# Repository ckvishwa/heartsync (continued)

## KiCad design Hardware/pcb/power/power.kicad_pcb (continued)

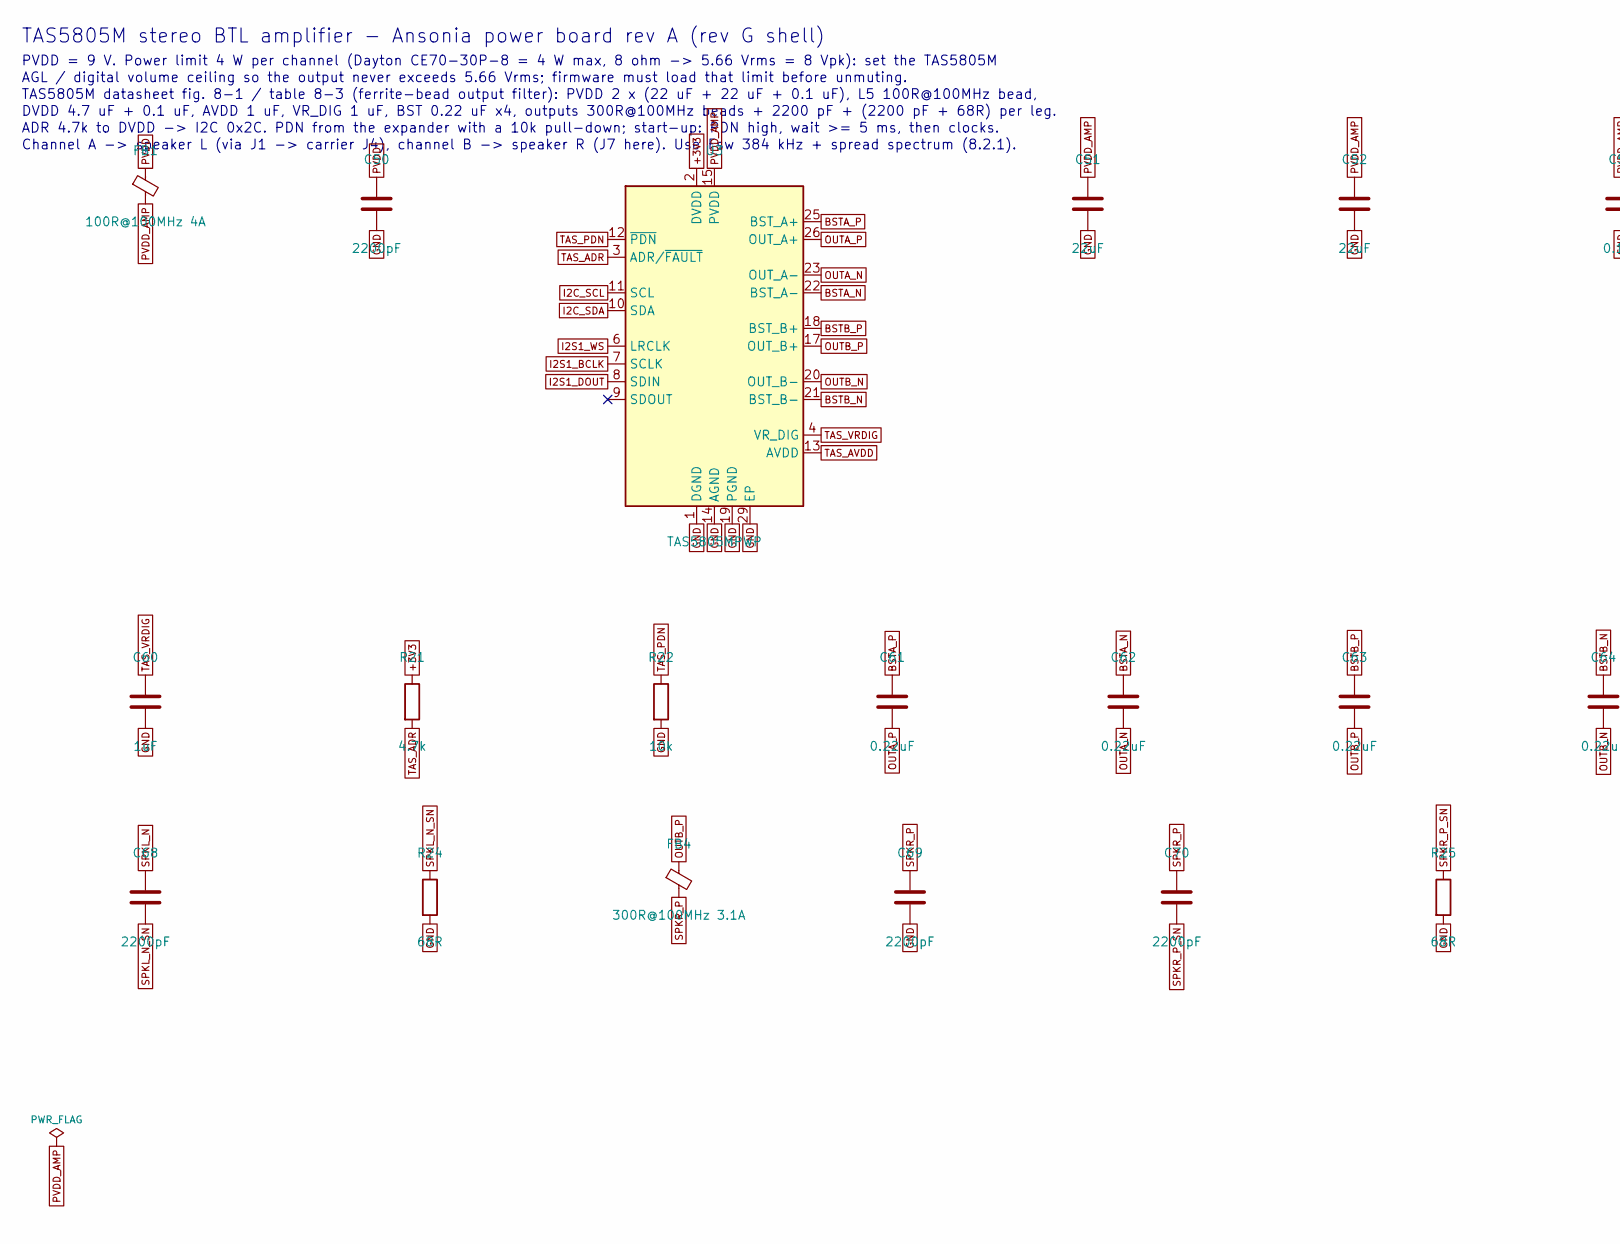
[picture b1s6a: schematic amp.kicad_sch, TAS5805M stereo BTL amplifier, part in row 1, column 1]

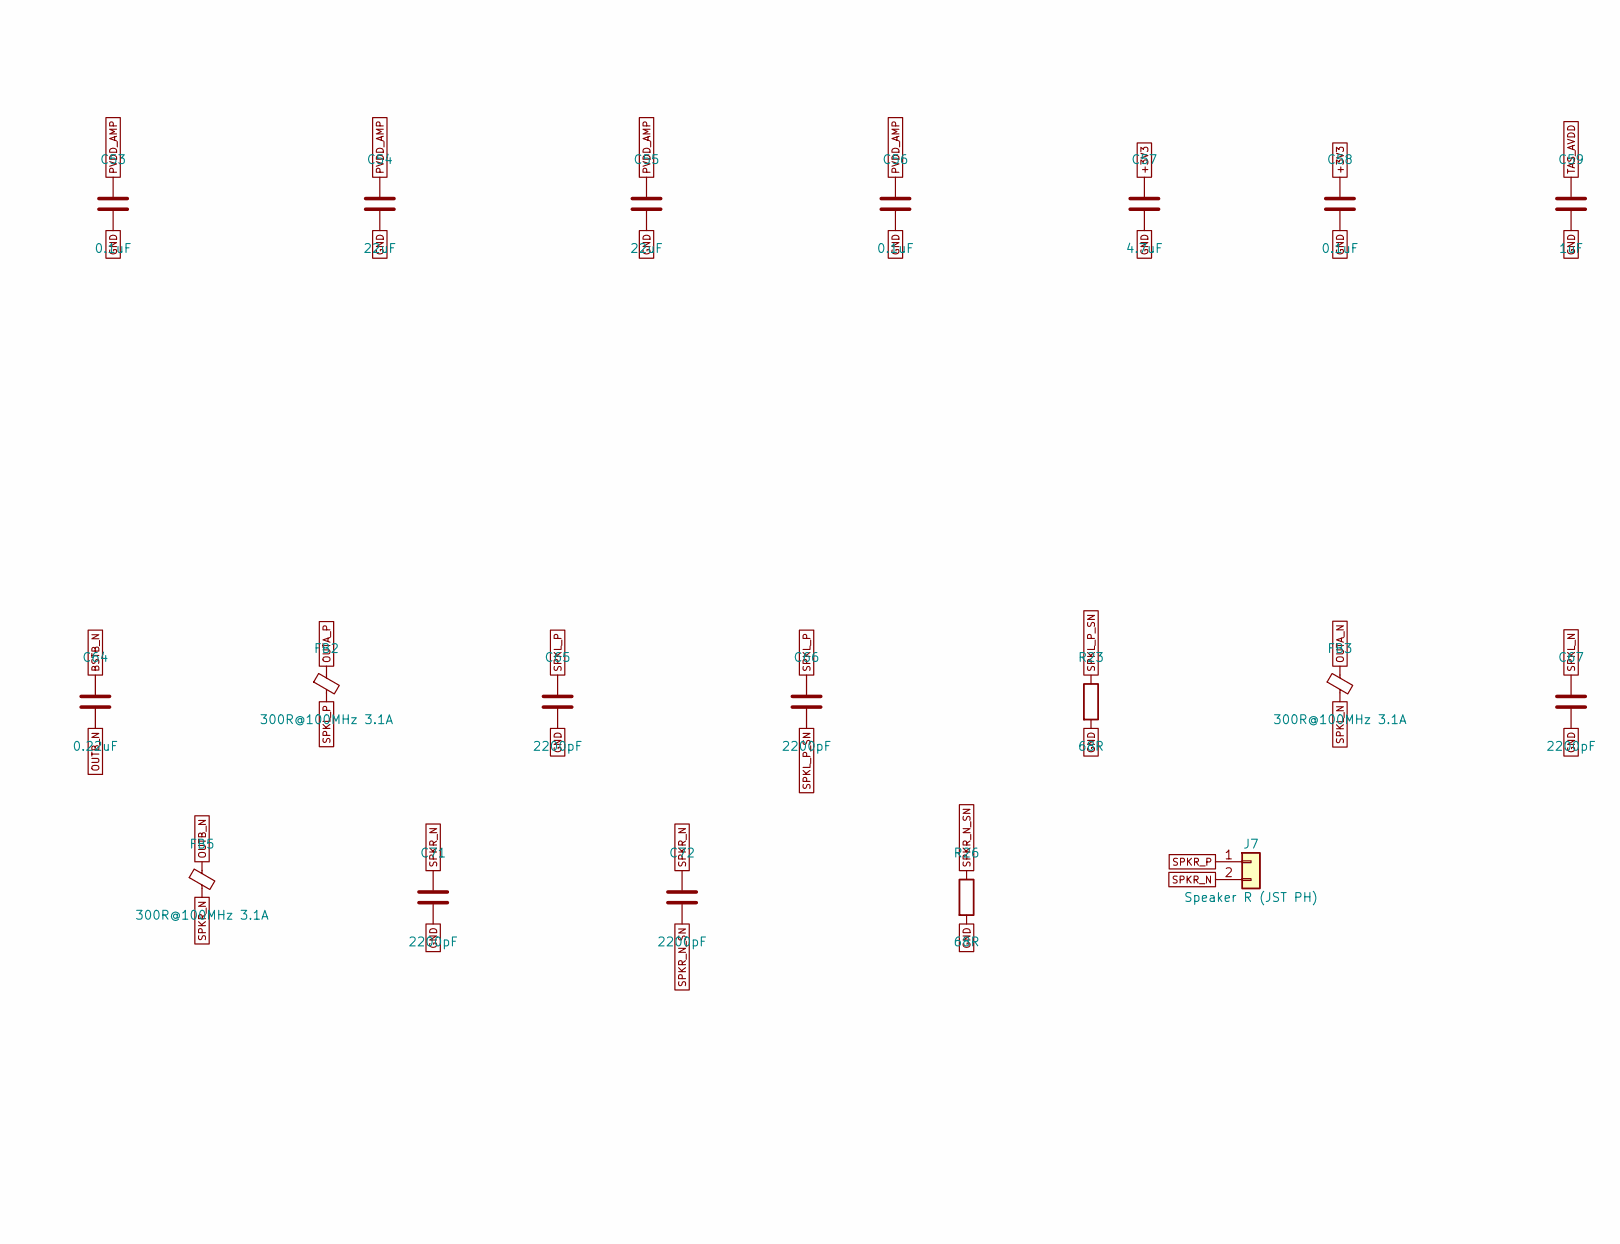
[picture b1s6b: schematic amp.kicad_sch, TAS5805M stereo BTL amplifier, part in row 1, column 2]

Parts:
C50: 2200pF; C_0402_1005Metric
C51, C52, C54, C55: 22uF; C_0805_2012Metric
C53, C56, C58: 0.1uF; C_0402_1005Metric
C57: 4.7uF; C_0603_1608Metric
C59, C60: 1uF; C_0603_1608Metric
C61, C62, C63, C64: 0.22uF; C_0603_1608Metric
C65, C66, C67, C68, C69, C70, C71, C72: 2200pF; C_0603_1608Metric
FB1: 100R@100MHz 4A; L_0805_2012Metric
FB2, FB3, FB4, FB5: 300R@100MHz 3.1A; L_0805_2012Metric
J7: Speaker R (JST PH); JST_PH_S2B-PH-SM4-TB_1x02-1MP_P2.00mm_Horizontal
R21: 4.7k; R_0402_1005Metric
R22: 10k; R_0402_1005Metric
R23, R24, R25, R26: 68R; R_0603_1608Metric
U3: TAS5805MPWP; TI_PWP0028M_HTSSOP-28_ThermalVias_0.3; MPN TAS5805MPWPR; LCSC C2059816

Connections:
+3V3: C57.1, C58.1, R21.1, U3.2 (DVDD); also elsewhere on the board
BSTA_N: C62.1, U3.22 (BST_A-)
BSTA_P: C61.1, U3.25 (BST_A+)
BSTB_N: C64.1, U3.21 (BST_B-)
BSTB_P: C63.1, U3.18 (BST_B+)
GND: C50.2, C51.2, C52.2, C53.2, C54.2, C55.2, C56.2, C57.2, C58.2, C59.2, C60.2, C65.2, C67.2, C69.2, C71.2, R22.2, R23.2, R24.2, R25.2, R26.2, U3.1 (DGND), U3.5 (DGND), U3.14 (AGND), U3.19 (PGND), U3.24 (PGND), U3.29 (EP); also elsewhere on the board
I2C_SCL: U3.11 (SCL); also elsewhere on the board
I2C_SDA: U3.10 (SDA); also elsewhere on the board
I2S1_BCLK: U3.7 (SCLK); also elsewhere on the board
I2S1_DOUT: U3.8 (SDIN); also elsewhere on the board
I2S1_WS: U3.6 (LRCLK); also elsewhere on the board
OUTA_N: C62.2, FB3.1, U3.23 (OUT_A-)
OUTA_P: C61.2, FB2.1, U3.26 (OUT_A+)
OUTB_N: C64.2, FB5.1, U3.20 (OUT_B-)
OUTB_P: C63.2, FB4.1, U3.17 (OUT_B+)
PVDD: C50.1, FB1.1; also elsewhere on the board
PVDD_AMP: C51.1, C52.1, C53.1, C54.1, C55.1, C56.1, FB1.2, U3.15 (PVDD), U3.16 (PVDD), U3.27 (PVDD), U3.28 (PVDD)
SPKL_N: C67.1, C68.1, FB3.2; also elsewhere on the board
SPKL_N_SN: C68.2, R24.1
SPKL_P: C65.1, C66.1, FB2.2; also elsewhere on the board
SPKL_P_SN: C66.2, R23.1
SPKR_N: C71.1, C72.1, FB5.2, J7.2
SPKR_N_SN: C72.2, R26.1
SPKR_P: C69.1, C70.1, FB4.2, J7.1
SPKR_P_SN: C70.2, R25.1
TAS_ADR: R21.2, U3.3 (ADR/~FAULT)
TAS_AVDD: C59.1, U3.13 (AVDD)
TAS_PDN: R22.1, U3.12 (~PDN); also elsewhere on the board
TAS_VRDIG: C60.1, U3.4 (VR_DIG)

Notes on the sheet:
TAS5805M stereo BTL amplifier - Ansonia power board rev A (rev G shell)
PVDD = 9 V. Power limit 4 W per channel (Dayton CE70-30P-8 = 4 W max, 8 ohm -> 5.66 Vrms = 8 Vpk): set the TAS5805M
AGL / digital volume ceiling so the output never exceeds 5.66 Vrms; firmware must load that limit before unmuting.
TAS5805M datasheet fig. 8-1 / table 8-3 (ferrite-bead output filter): PVDD 2 x (22 uF + 22 uF + 0.1 uF), L5 100R@100MHz bead,
DVDD 4.7 uF + 0.1 uF, AVDD 1 uF, VR_DIG 1 uF, BST 0.22 uF x4, outputs 300R@100MHz beads + 2200 pF + (2200 pF + 68R) per leg.
ADR 4.7k to DVDD -> I2C 0x2C. PDN from the expander with a 10k pull-down; start-up: PDN high, wait >= 5 ms, then clocks.
Channel A -> speaker L (via J1 -> carrier J4), channel B -> speaker R (J7 here). Use Fsw 384 kHz + spread spectrum (8.2.1).

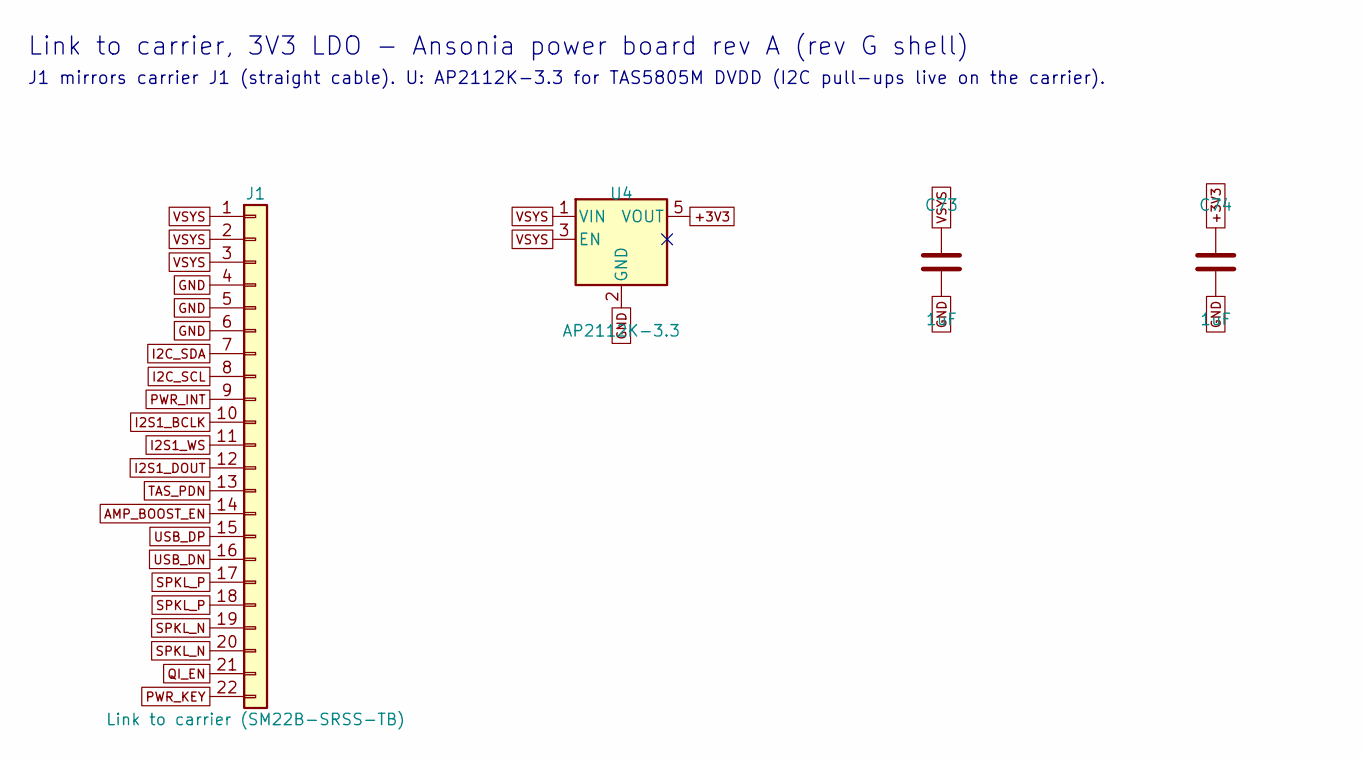
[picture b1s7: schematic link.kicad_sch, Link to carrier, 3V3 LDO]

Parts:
C73, C74: 1uF; C_0402_1005Metric
J1: Link to carrier (SM22B-SRSS-TB); JST_SH_SM22B-SRSS-TB_1x22-1MP_P1.00mm_Horizontal
U4: AP2112K-3.3; SOT-23-5; MPN AP2112K-3.3TRG1; LCSC C51118

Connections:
+3V3: C74.1, U4.5 (VOUT); also elsewhere on the board
AMP_BOOST_EN: J1.14; also elsewhere on the board
GND: C73.2, C74.2, J1.4, J1.5, J1.6, U4.2 (GND); also elsewhere on the board
I2C_SCL: J1.8; also elsewhere on the board
I2C_SDA: J1.7; also elsewhere on the board
I2S1_BCLK: J1.10; also elsewhere on the board
I2S1_DOUT: J1.12; also elsewhere on the board
I2S1_WS: J1.11; also elsewhere on the board
PWR_INT: J1.9; also elsewhere on the board
PWR_KEY: J1.22; also elsewhere on the board
QI_EN: J1.21; also elsewhere on the board
SPKL_N: J1.19, J1.20; also elsewhere on the board
SPKL_P: J1.17, J1.18; also elsewhere on the board
TAS_PDN: J1.13; also elsewhere on the board
USB_DN: J1.16; also elsewhere on the board
USB_DP: J1.15; also elsewhere on the board
VSYS: C73.1, J1.1, J1.2, J1.3, U4.1 (VIN), U4.3 (EN); also elsewhere on the board

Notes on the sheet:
Link to carrier, 3V3 LDO - Ansonia power board rev A (rev G shell)
J1 mirrors carrier J1 (straight cable). U: AP2112K-3.3 for TAS5805M DVDD (I2C pull-ups live on the carrier).

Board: 4 copper layers, 130 parts (38 on the bottom side), 74 nets, no tracks yet.

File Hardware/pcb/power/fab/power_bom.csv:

Comment,Designator,Footprint,LCSC Part #,MPN,Qty
10uF,"C1,C2,C48,C49",C_0805_2012Metric,,,4
10uF,"C24,C37",C_0603_1608Metric,,,2
4.7uF,"C27,C40,C57",C_0603_1608Metric,,,3
47nF,"C28,C41",C_0402_1005Metric,,,2
8.2nF,"C29,C42",C_0402_1005Metric,,,2
2.2uF,"C15,C16,C18,C19,C3",C_0603_1608Metric,,,5
22uF,"C31,C32,C33,C44,C45,C46",C_1206_3216Metric,,,6
1uF,"C34,C47,C59,C60",C_0603_1608Metric,,,4
0.1uF,"C11,C13,C14,C17,C20,C25,C26,C38,C39,C4,C53,C56,C58",C_0402_1005Metric,,,13
22uF,"C10,C12,C21,C22,C23,C35,C36,C5,C51,C52,C54,C55,C6,C7,C8,C9",C_0805_2012Metric,,,16
2200pF,C50,C_0402_1005Metric,,,1
0.22uF,"C61,C62,C63,C64",C_0603_1608Metric,,,4
2200pF,"C65,C66,C67,C68,C69,C70,C71,C72",C_0603_1608Metric,,,8
1uF,"C73,C74",C_0402_1005Metric,,,2
SMF22A,"D1,D2",D_SOD-123F,,,2
SMF5.0A,D3,D_SOD-123F,,,1
8A fast,F1,Fuse_1206_3216Metric,,0466008.NR,1
100R@100MHz 4A,FB1,L_0805_2012Metric,,,1
300R@100MHz 3.1A,"FB2,FB3,FB4,FB5",L_0805_2012Metric,,,4
Link to carrier (SM22B-SRSS-TB),J1,JST_SH_SM22B-SRSS-TB_1x22-1MP_P1.00mm_Horizontal,,,1
"124019572112A (port 1, in/out)",J2,USB_C_Amphenol_124019572112A,,124019572112A,1
"124019572112A (port 2, out)",J3,USB_C_Amphenol_124019572112A,,124019572112A,1
"Cell: Amass MR30PW-M (3-pole; pins 1 = BAT+, 3 = BAT-, 2 open)",J4,Amass_MR30PW-M_1x03_P3.50mm_Horizontal,,MR30PW-M,1
Cell NTC (JST SH 2),J5,JST_SH_SM02B-SRSS-TB_1x02-1MP_P1.00mm_Horizontal,,,1
"Qi TX module 24x32 (9 V, 2 contacts per leg)",J6,JST_SH_SM04B-SRSS-TB_1x04-1MP_P1.00mm_Horizontal,,,1
Speaker R (JST PH),J7,JST_PH_S2B-PH-SM4-TB_1x02-1MP_P2.00mm_Horizontal,,,1
2.2uH,"L1,L2,L3",L_Bourns_SRP7028A_7.3x6.6mm,,SRP7028A-2R2M,3
1uH,L4,L_1210_3225Metric,,DFE322520F-1R0M,1
DMP3013SFV,Q1,Diodes_PowerDI3333-8,,,1
3.3k,"R1,R2",R_0402_1005Metric,,,2
232k,"R10,R16",R_0402_1005Metric,,,2
49.9k,"R11,R17",R_0402_1005Metric,,,2
23.7k,"R12,R18",R_0402_1005Metric,,,2
499k,"R13,R19",R_0402_1005Metric,,,2
76.8k,"R14,R20",R_0402_1005Metric,,,2
4.7k,R21,R_0402_1005Metric,,,1
68R,"R23,R24,R25,R26",R_0603_1608Metric,,,4
510k,R3,R_0402_1005Metric,,,1
22.1k,R4,R_0402_1005Metric,,,1
22k,"R5,R6",R_0402_1005Metric,,,2
10k,"R15,R22,R7,R9",R_0402_1005Metric,,,4
0R,R8,R_1206_3216Metric,,,1
IP5356M_LBZ_CB,U1,QFN-40-1EP_6x6mm_P0.5mm_EP4.6x4.6mm,C46550232,IP5356M_LBZ_CB,1
TPS61088RHLR,"U2,U7",Texas_VQFN-RHL-20,C88281,TPS61088RHLR,2
TAS5805MPWP,U3,TI_PWP0028M_HTSSOP-28_ThermalVias_0.3,C2059816,TAS5805MPWPR,1
AP2112K-3.3,U4,SOT-23-5,C51118,AP2112K-3.3TRG1,1
TPD4E05U06DQA,"U5,U6",USON-10_2.5x1.0mm_P0.5mm,,TPD4E05U06DQAR,2

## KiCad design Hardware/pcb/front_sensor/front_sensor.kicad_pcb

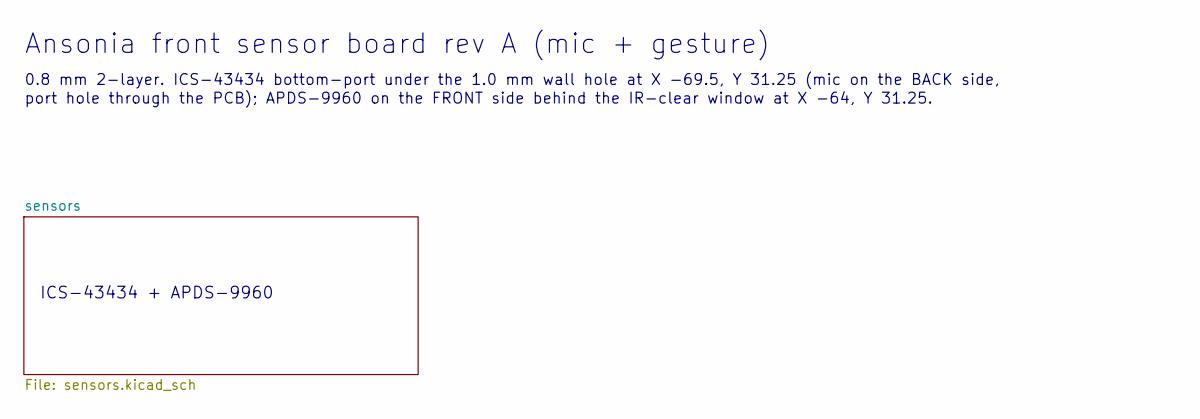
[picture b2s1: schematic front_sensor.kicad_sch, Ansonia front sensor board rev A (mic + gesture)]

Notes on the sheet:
ICS-43434 + APDS-9960
Ansonia front sensor board rev A (mic + gesture)
0.8 mm 2-layer. ICS-43434 bottom-port under the 1.0 mm wall hole at X -69.5, Y 31.25 (mic on the BACK side,
port hole through the PCB); APDS-9960 on the FRONT side behind the IR-clear window at X -64, Y 31.25.

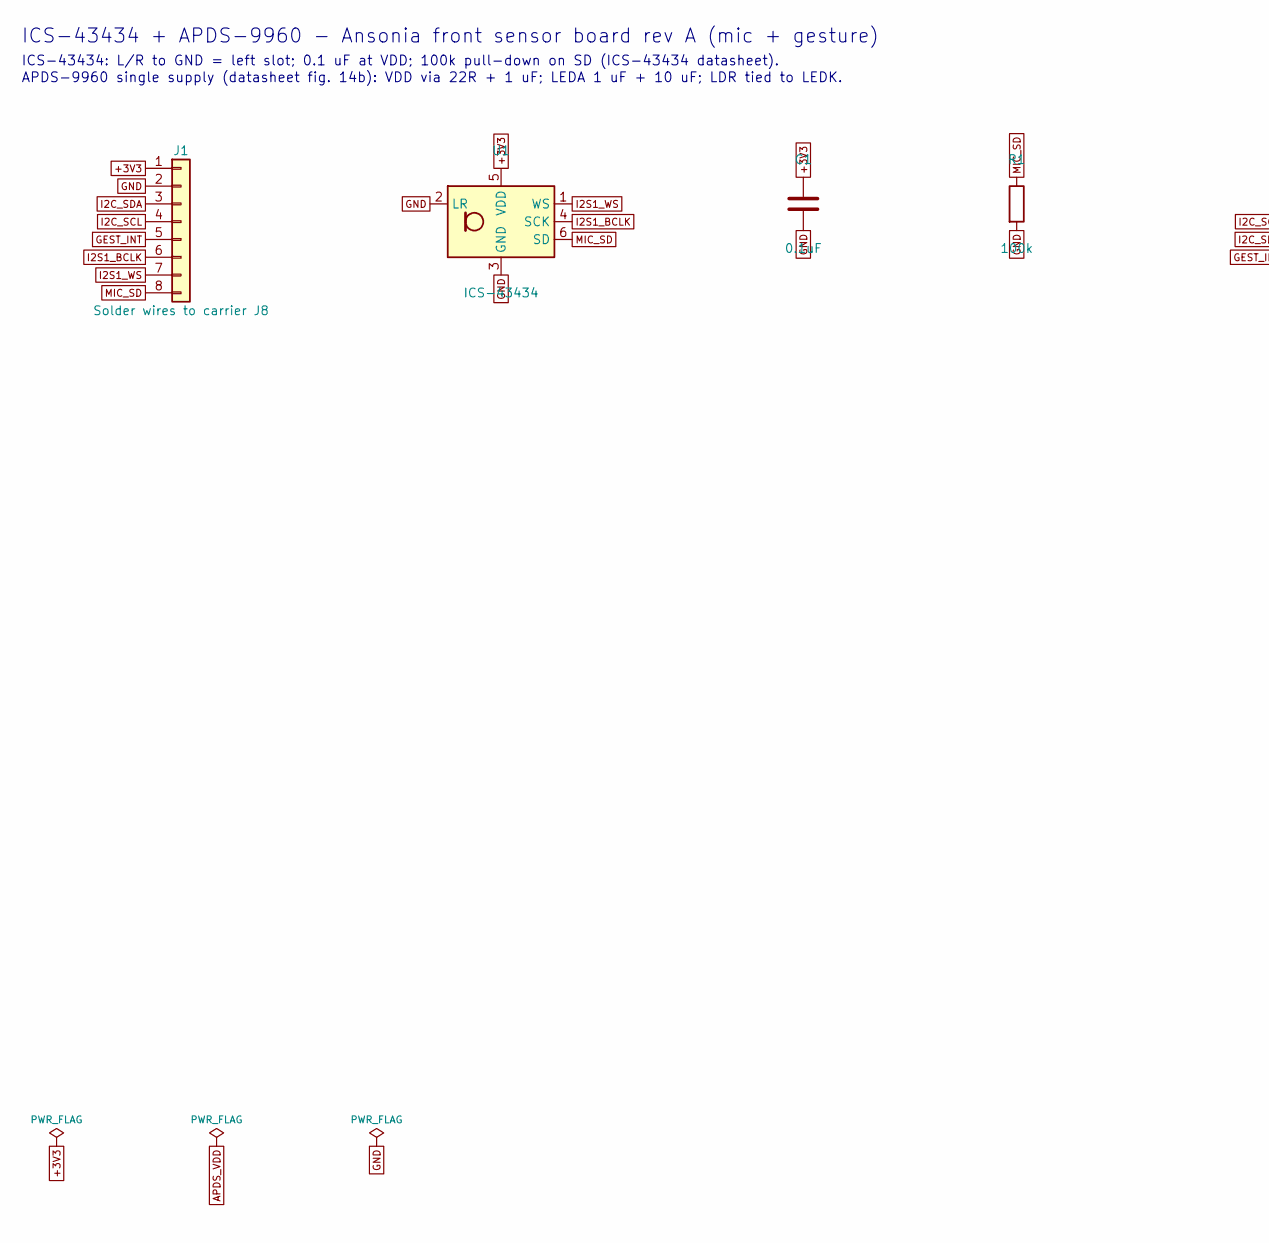
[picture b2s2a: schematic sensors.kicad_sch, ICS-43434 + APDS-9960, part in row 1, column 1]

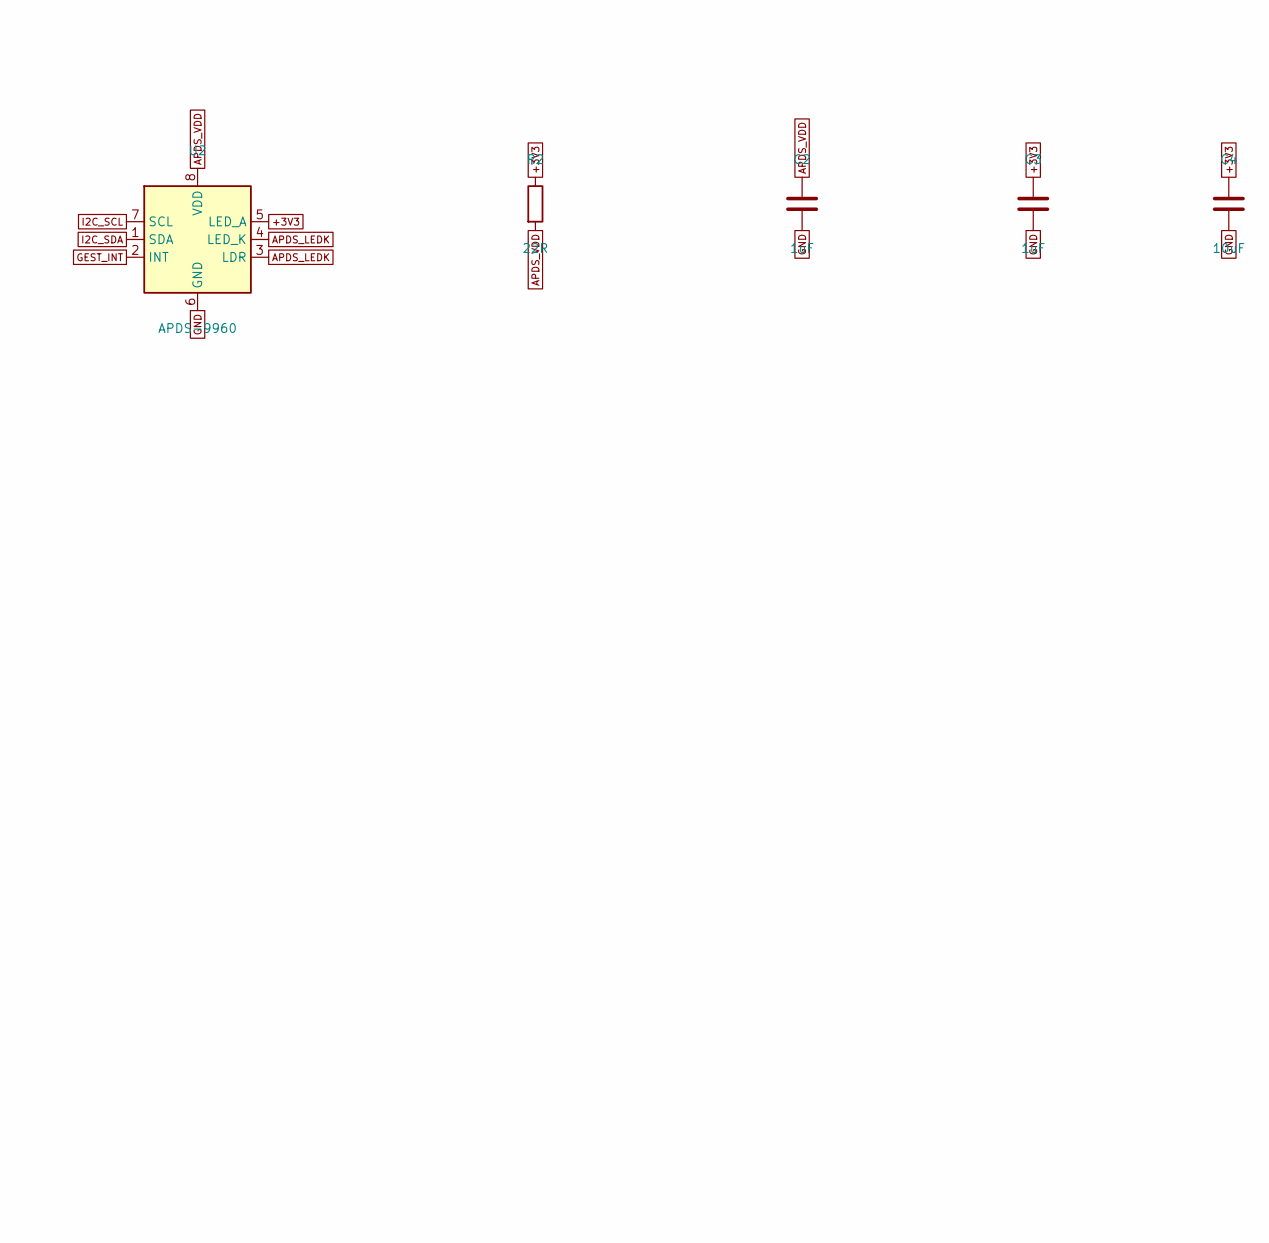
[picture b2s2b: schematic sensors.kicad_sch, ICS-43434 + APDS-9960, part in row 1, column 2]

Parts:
C1: 0.1uF; C_0402_1005Metric
C2, C3: 1uF; C_0402_1005Metric
C4: 10uF; C_0603_1608Metric
J1: Solder wires to carrier J8; WirePads_1x08_P1.20mm
R1: 100k; R_0402_1005Metric
R2: 22R; R_0402_1005Metric
U1: ICS-43434; InvenSense_ICS-43434-6_3.5x2.65mm; MPN ICS-43434
U2: APDS-9960; Avago_APDS-9960; MPN APDS-9960

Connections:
+3V3: C1.1, C3.1, C4.1, J1.1, R2.1, U1.5 (VDD), U2.5 (LED_A)
APDS_LEDK: U2.3 (LDR), U2.4 (LED_K)
APDS_VDD: C2.1, R2.2, U2.8 (VDD)
GEST_INT: J1.5, U2.2 (INT)
GND: C1.2, C2.2, C3.2, C4.2, J1.2, R1.2, U1.2 (LR), U1.3 (GND), U2.6 (GND)
I2C_SCL: J1.4, U2.7 (SCL)
I2C_SDA: J1.3, U2.1 (SDA)
I2S1_BCLK: J1.6, U1.4 (SCK)
I2S1_WS: J1.7, U1.1 (WS)
MIC_SD: J1.8, R1.1, U1.6 (SD)

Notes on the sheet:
ICS-43434 + APDS-9960 - Ansonia front sensor board rev A (mic + gesture)
ICS-43434: L/R to GND = left slot; 0.1 uF at VDD; 100k pull-down on SD (ICS-43434 datasheet).
APDS-9960 single supply (datasheet fig. 14b): VDD via 22R + 1 uF; LEDA 1 uF + 10 uF; LDR tied to LEDK.

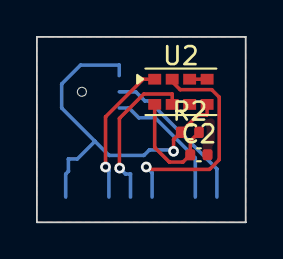
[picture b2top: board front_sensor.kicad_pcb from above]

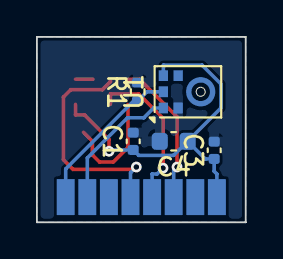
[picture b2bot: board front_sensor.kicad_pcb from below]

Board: 2 copper layers, 11.6 x 10.3 mm, 9 parts (6 on the bottom side), 10 nets.

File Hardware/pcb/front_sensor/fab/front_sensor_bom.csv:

Comment,Designator,Footprint,LCSC Part #,MPN,Qty
0.1uF,C1,C_0402_1005Metric,,,1
1uF,"C2,C3",C_0402_1005Metric,,,2
10uF,C4,C_0603_1608Metric,,,1
Solder wires to carrier J8,J1,WirePads_1x08_P1.20mm,,,1
100k,R1,R_0402_1005Metric,,,1
22R,R2,R_0402_1005Metric,,,1
ICS-43434,U1,InvenSense_ICS-43434-6_3.5x2.65mm,,ICS-43434,1
APDS-9960,U2,Avago_APDS-9960,,APDS-9960,1

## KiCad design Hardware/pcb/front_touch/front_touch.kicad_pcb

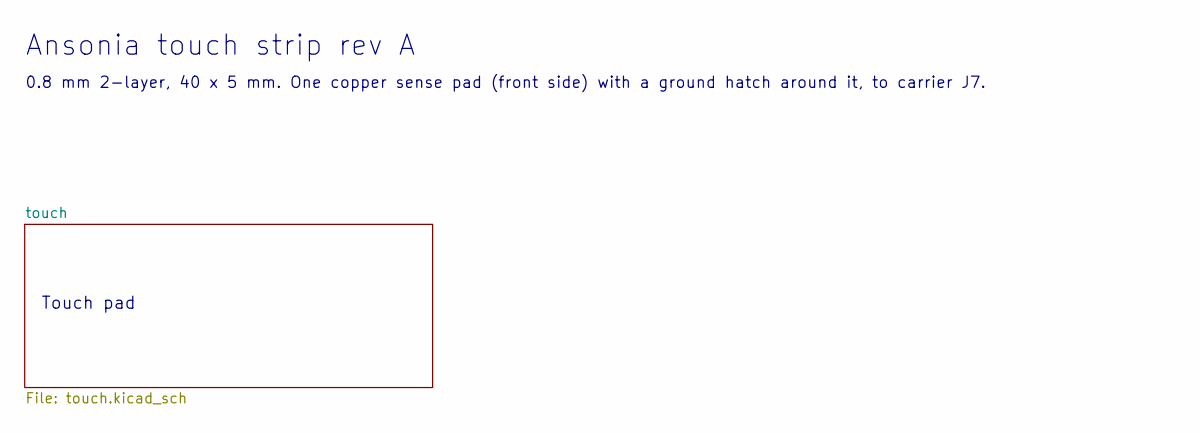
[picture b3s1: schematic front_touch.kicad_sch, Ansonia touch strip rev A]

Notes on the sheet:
Touch pad
Ansonia touch strip rev A
0.8 mm 2-layer, 40 x 5 mm. One copper sense pad (front side) with a ground hatch around it, to carrier J7.

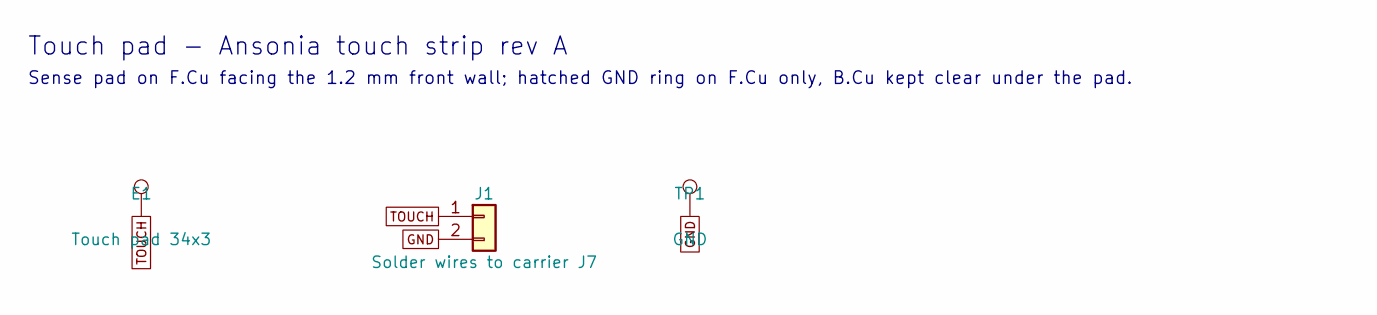
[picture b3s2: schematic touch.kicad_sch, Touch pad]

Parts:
E1: Touch pad 34x3; TouchPad_34x3
J1: Solder wires to carrier J7; WirePads_1x02_P1.60mm
TP1: GND; TestPoint_Pad_D1.0mm

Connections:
GND: J1.2, TP1.1
TOUCH: E1.1, J1.1

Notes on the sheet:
Touch pad - Ansonia touch strip rev A
Sense pad on F.Cu facing the 1.2 mm front wall; hatched GND ring on F.Cu only, B.Cu kept clear under the pad.

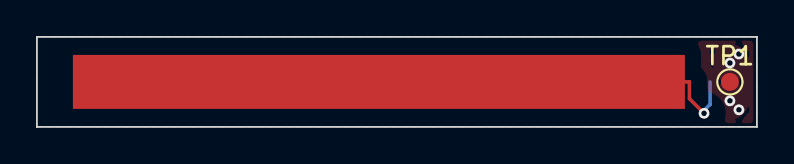
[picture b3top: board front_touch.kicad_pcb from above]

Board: 2 copper layers, 40.0 x 5.0 mm, 3 parts (1 on the bottom side), 2 nets.

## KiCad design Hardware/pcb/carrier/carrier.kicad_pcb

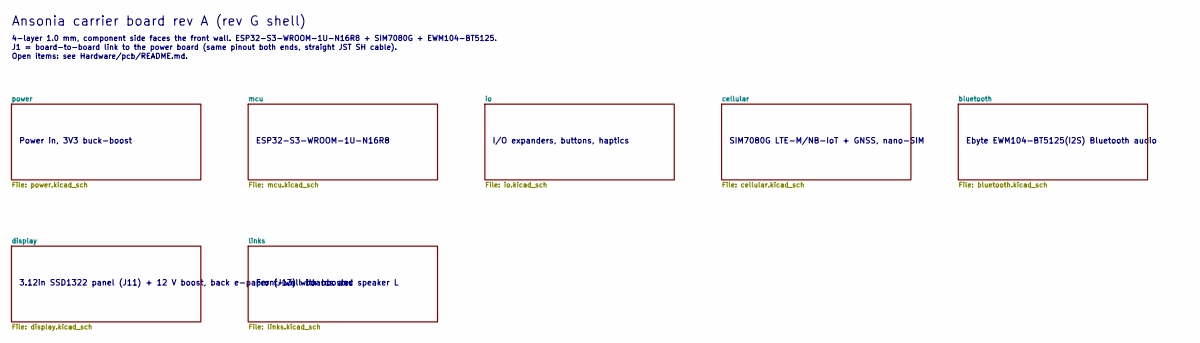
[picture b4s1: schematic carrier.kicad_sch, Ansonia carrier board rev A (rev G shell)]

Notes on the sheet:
Power in, 3V3 buck-boost
ESP32-S3-WROOM-1U-N16R8
I/O expanders, buttons, haptics
SIM7080G LTE-M/NB-IoT + GNSS, nano-SIM
Ebyte EWM104-BT5125(I2S) Bluetooth audio
3.12in SSD1322 panel (J11) + 12 V boost, back e-paper (J13) with booster
Front-wall boards and speaker L
Ansonia carrier board rev A (rev G shell)
4-layer 1.0 mm, component side faces the front wall. ESP32-S3-WROOM-1U-N16R8 + SIM7080G + EWM104-BT5125.
J1 = board-to-board link to the power board (same pinout both ends, straight JST SH cable).
Open items: see Hardware/pcb/README.md.

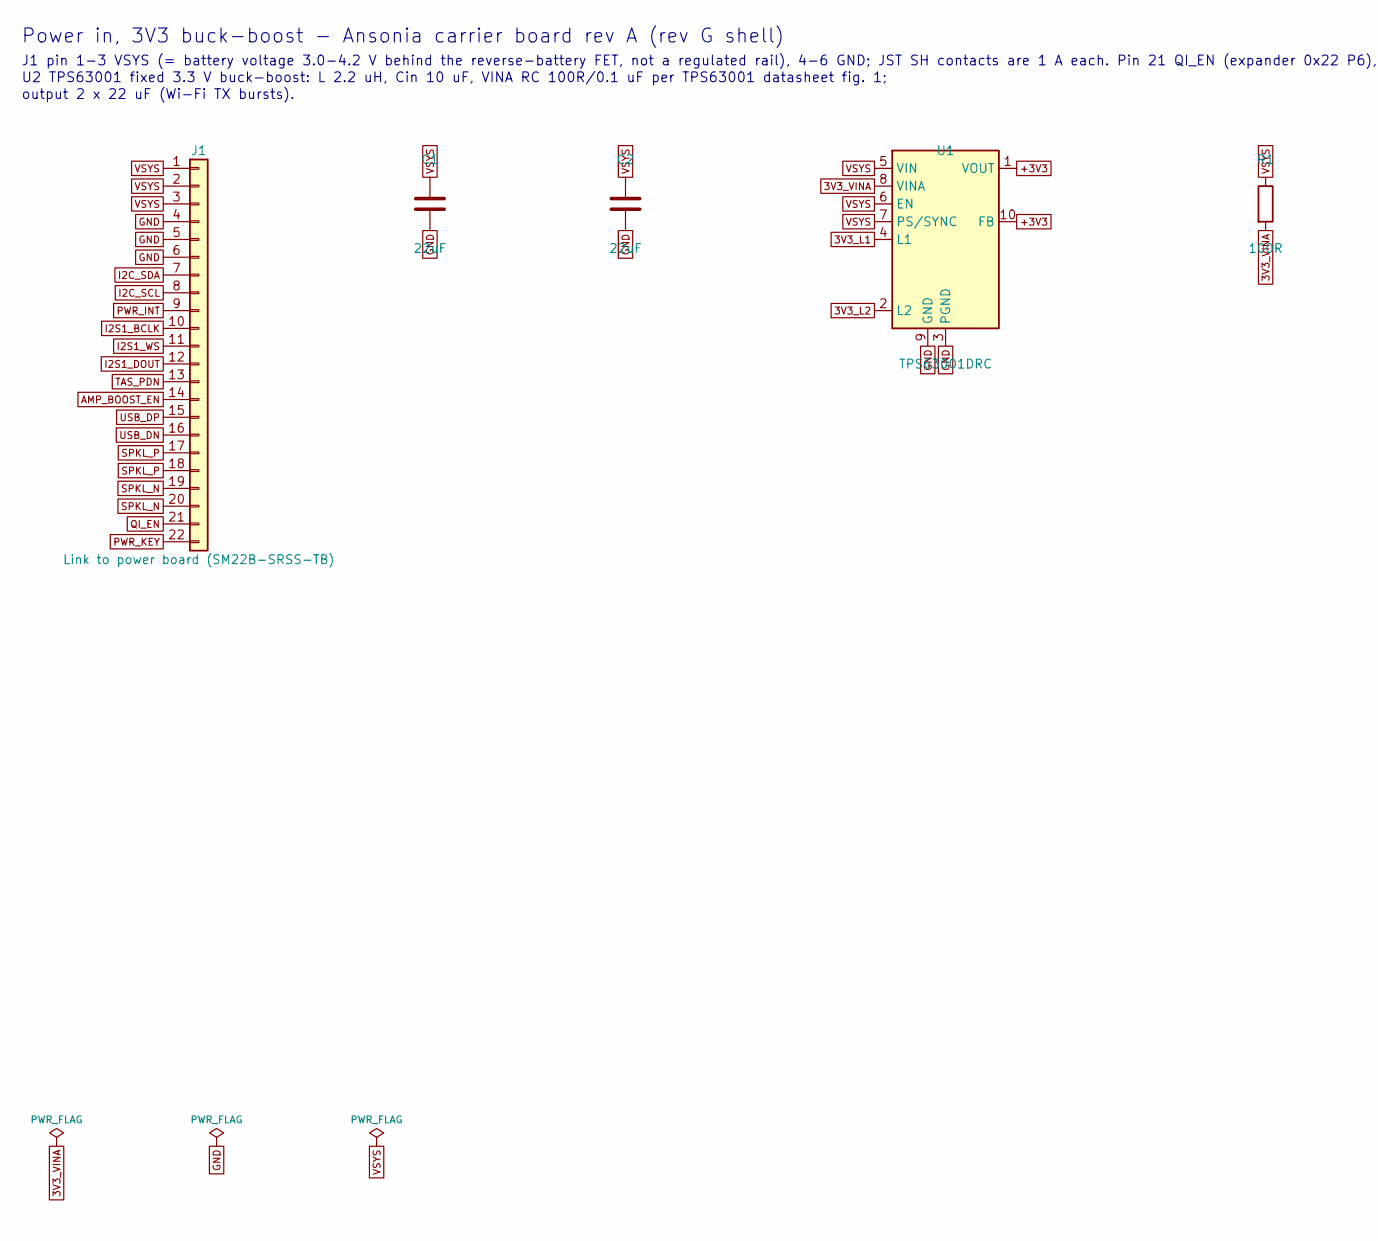
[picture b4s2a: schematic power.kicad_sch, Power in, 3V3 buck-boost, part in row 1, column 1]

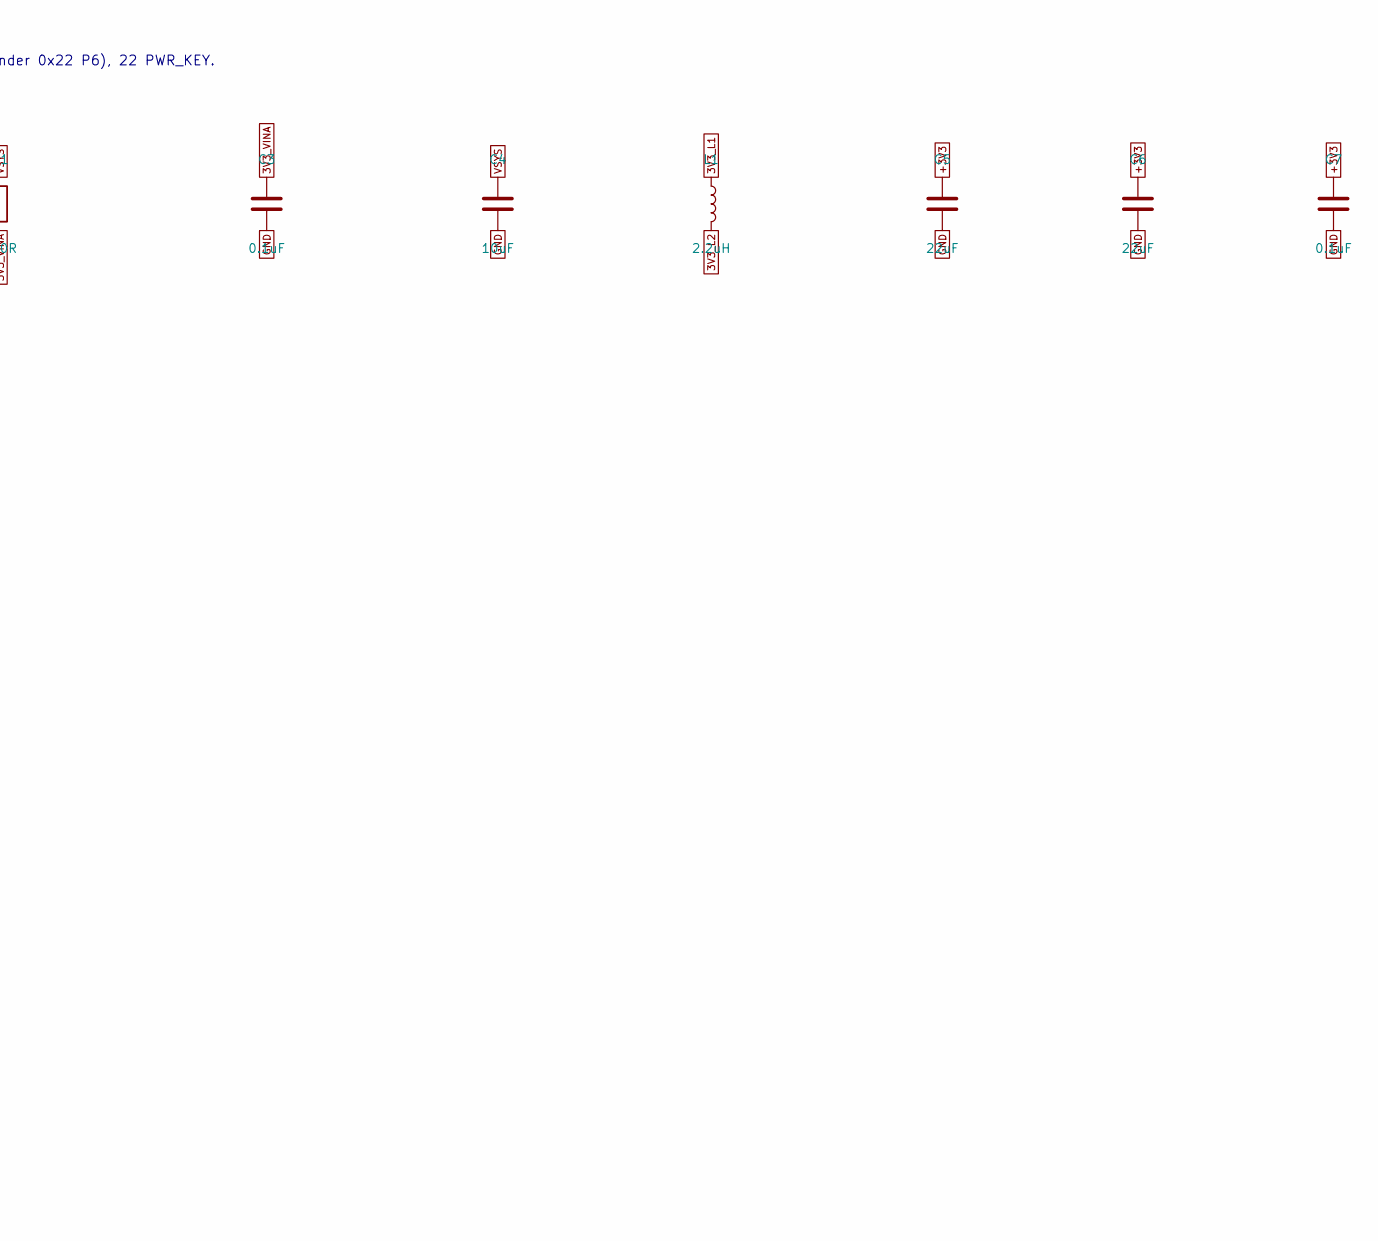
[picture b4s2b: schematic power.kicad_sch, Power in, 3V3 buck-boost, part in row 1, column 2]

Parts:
C1, C2, C5, C6: 22uF; C_0805_2012Metric
C3, C7: 0.1uF; C_0402_1005Metric
C4: 10uF; C_0603_1608Metric
J1: Link to power board (SM22B-SRSS-TB); JST_SH_SM22B-SRSS-TB_1x22-1MP_P1.00mm_Horizontal
L1: 2.2uH; L_1008_2520Metric; MPN DFE252012F-2R2M=P2
R1: 100R; R_0402_1005Metric
U1: TPS63001DRC; Texas_DRC0010J; MPN TPS63001DRCR; LCSC C28855

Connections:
3V3_L1: L1.1, U1.4 (L1)
3V3_L2: L1.2, U1.2 (L2)
3V3_VINA: C3.1, R1.2, U1.8 (VINA)
+3V3: C5.1, C6.1, C7.1, U1.1 (VOUT), U1.10 (FB); also elsewhere on the board
AMP_BOOST_EN: J1.14; also elsewhere on the board
GND: C1.2, C2.2, C3.2, C4.2, C5.2, C6.2, C7.2, J1.4, J1.5, J1.6, U1.3 (PGND), U1.9 (GND), U1.11 (PGND); also elsewhere on the board
I2C_SCL: J1.8; also elsewhere on the board
I2C_SDA: J1.7; also elsewhere on the board
I2S1_BCLK: J1.10; also elsewhere on the board
I2S1_DOUT: J1.12; also elsewhere on the board
I2S1_WS: J1.11; also elsewhere on the board
PWR_INT: J1.9; also elsewhere on the board
PWR_KEY: J1.22; also elsewhere on the board
QI_EN: J1.21; also elsewhere on the board
SPKL_N: J1.19, J1.20; also elsewhere on the board
SPKL_P: J1.17, J1.18; also elsewhere on the board
TAS_PDN: J1.13; also elsewhere on the board
USB_DN: J1.16; also elsewhere on the board
USB_DP: J1.15; also elsewhere on the board
VSYS: C1.1, C2.1, C4.1, J1.1, J1.2, J1.3, R1.1, U1.5 (VIN), U1.6 (EN), U1.7 (PS/SYNC); also elsewhere on the board

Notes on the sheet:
Power in, 3V3 buck-boost - Ansonia carrier board rev A (rev G shell)
J1 pin 1-3 VSYS (= battery voltage 3.0-4.2 V behind the reverse-battery FET, not a regulated rail), 4-6 GND; JST SH contacts are 1 A each. Pin 21 QI_EN (expander 0x22 P6), 22 PWR_KEY.
U2 TPS63001 fixed 3.3 V buck-boost: L 2.2 uH, Cin 10 uF, VINA RC 100R/0.1 uF per TPS63001 datasheet fig. 1;
output 2 x 22 uF (Wi-Fi TX bursts).
